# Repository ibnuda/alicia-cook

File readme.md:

# alicia cook

yet another uninspiring, boring, and beaten to death clone of alice "ergonomic"
keyboard. lol.

but, you should actually split it off and connect them using idc 2x5, tho.

## pics

## license
of course it's GPLv3.

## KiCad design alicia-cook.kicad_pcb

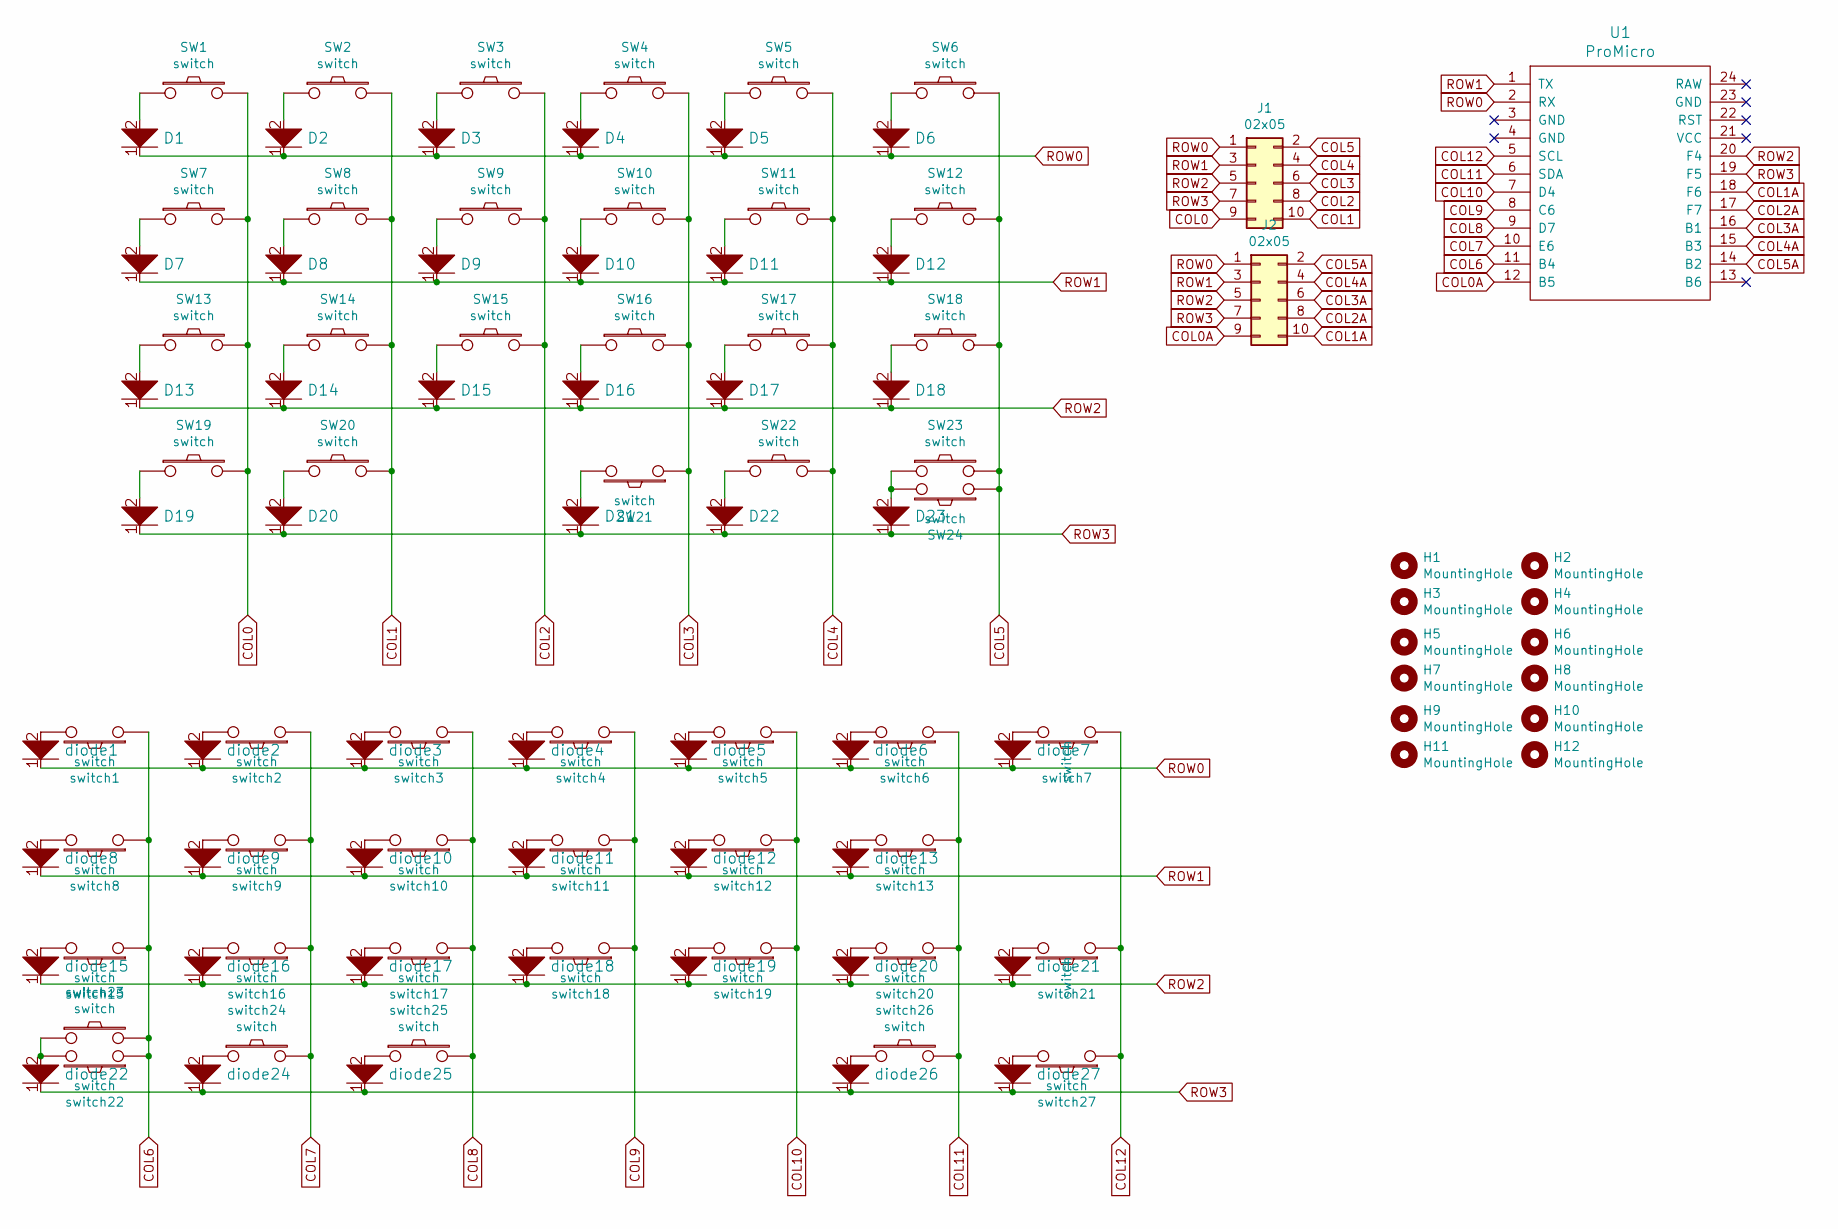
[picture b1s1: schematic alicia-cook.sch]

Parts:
D1, D2, D3, D4, D5, D6, D7, D8, D9, D10, D11, D12, D13, D14, D15, D16, D17, D18, D19, D20, D21, D22, D23: D; diode
H1, H3: MountingHole; hole-three-bigger
H2, H4, H5, H6, H7, H8, H9, H10, H11, H12: MountingHole; hole-three
J1, J2: 02x05; connector-shrouded
SW1, SW2, SW3, SW4, SW5, SW6, SW8, SW9, SW10, SW11, SW12, SW14, SW15, SW16, SW17, SW18, SW22, SW23: switch; 1u-minimal
SW7, SW19, SW20, SW21: switch; 125u-minimal
SW13: switch; 175u-minimal
SW24: switch; 2u-minimal
U1: ProMicro; promicro
diode1, diode2, diode3, diode4, diode5, diode6, diode7, diode8, diode9, diode10, diode11, diode12, diode13, diode15, diode16, diode17, diode18, diode19, diode20, diode21, diode22, diode24, diode25, diode26, diode27: diode
switch1, switch2, switch3, switch4, switch5, switch6, switch7, switch8, switch9, switch10, switch11, switch12, switch15, switch16, switch17, switch18, switch19, switch20, switch24, switch25: switch; 1u-minimal
switch13: switch; 175u-minimal
switch21, switch22, switch26, switch27: switch; 125u-minimal
switch23: switch; 225u-minimal

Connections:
COL0: J1.9, SW1.2, SW7.2, SW13.2, SW19.2
COL0A: J2.9, U1.12 (B5)
COL1: J1.10, SW2.2, SW8.2, SW14.2, SW20.2
COL1A: J2.10, U1.18 (F6)
COL2: J1.8, SW3.2, SW9.2, SW15.2
COL2A: J2.8, U1.17 (F7)
COL3: J1.6, SW4.2, SW10.2, SW16.2, SW21.1
COL3A: J2.6, U1.16 (B1)
COL4: J1.4, SW5.2, SW11.2, SW17.2, SW22.2
COL4A: J2.4, U1.15 (B3)
COL5: J1.2, SW6.2, SW12.2, SW18.2, SW23.2, SW24.1
COL5A: J2.2, U1.14 (B2)
COL6: U1.11 (B4), switch1.1, switch8.1, switch15.1, switch22.1, switch23.2
COL7: U1.10 (E6), switch2.1, switch9.1, switch16.1, switch24.2
COL8: U1.9 (D7), switch3.1, switch10.1, switch17.1, switch25.2
COL9: U1.8 (C6), switch4.1, switch11.1, switch18.1
COL10: U1.7 (D4), switch5.1, switch12.1, switch19.1
COL11: U1.6 (SDA), switch6.1, switch13.1, switch20.1, switch26.2
COL12: U1.5 (SCL), switch7.1, switch21.1, switch27.1
unnamed: D1.2, SW1.1
unnamed: D2.2, SW2.1
unnamed: D3.2, SW3.1
unnamed: D4.2, SW4.1
unnamed: D5.2, SW5.1
unnamed: D6.2, SW6.1
unnamed: D7.2, SW7.1
unnamed: D8.2, SW8.1
unnamed: D9.2, SW9.1
unnamed: D10.2, SW10.1
unnamed: D11.2, SW11.1
unnamed: D12.2, SW12.1
unnamed: D13.2, SW13.1
unnamed: D14.2, SW14.1
unnamed: D15.2, SW15.1
unnamed: D16.2, SW16.1
unnamed: D17.2, SW17.1
unnamed: D18.2, SW18.1
unnamed: D19.2, SW19.1
unnamed: D20.2, SW20.1
unnamed: D21.2, SW21.2
unnamed: D22.2, SW22.1
unnamed: D23.2, SW23.1, SW24.2
unnamed: diode1.2, switch1.2
unnamed: diode2.2, switch2.2
unnamed: diode3.2, switch3.2
unnamed: diode4.2, switch4.2
unnamed: diode5.2, switch5.2
unnamed: diode6.2, switch6.2
unnamed: diode7.2, switch7.2
unnamed: diode8.2, switch8.2
unnamed: diode9.2, switch9.2
unnamed: diode10.2, switch10.2
unnamed: diode11.2, switch11.2
unnamed: diode12.2, switch12.2
unnamed: diode13.2, switch13.2
unnamed: diode15.2, switch15.2
unnamed: diode16.2, switch16.2
unnamed: diode17.2, switch17.2
unnamed: diode18.2, switch18.2
unnamed: diode19.2, switch19.2
unnamed: diode20.2, switch20.2
unnamed: diode21.2, switch21.2
unnamed: diode22.2, switch22.2, switch23.1
unnamed: diode24.2, switch24.1
unnamed: diode25.2, switch25.1
unnamed: diode26.2, switch26.1
unnamed: diode27.2, switch27.2
ROW0: D1.1, D2.1, D3.1, D4.1, D5.1, D6.1, J1.1, J2.1, U1.2 (RX), diode1.1, diode2.1, diode3.1, diode4.1, diode5.1, diode6.1, diode7.1
ROW1: D7.1, D8.1, D9.1, D10.1, D11.1, D12.1, J1.3, J2.3, U1.1 (TX), diode8.1, diode9.1, diode10.1, diode11.1, diode12.1, diode13.1
ROW2: D13.1, D14.1, D15.1, D16.1, D17.1, D18.1, J1.5, J2.5, U1.20 (F4), diode15.1, diode16.1, diode17.1, diode18.1, diode19.1, diode20.1, diode21.1
ROW3: D19.1, D20.1, D21.1, D22.1, D23.1, J1.7, J2.7, U1.19 (F5), diode22.1, diode24.1, diode25.1, diode26.1, diode27.1

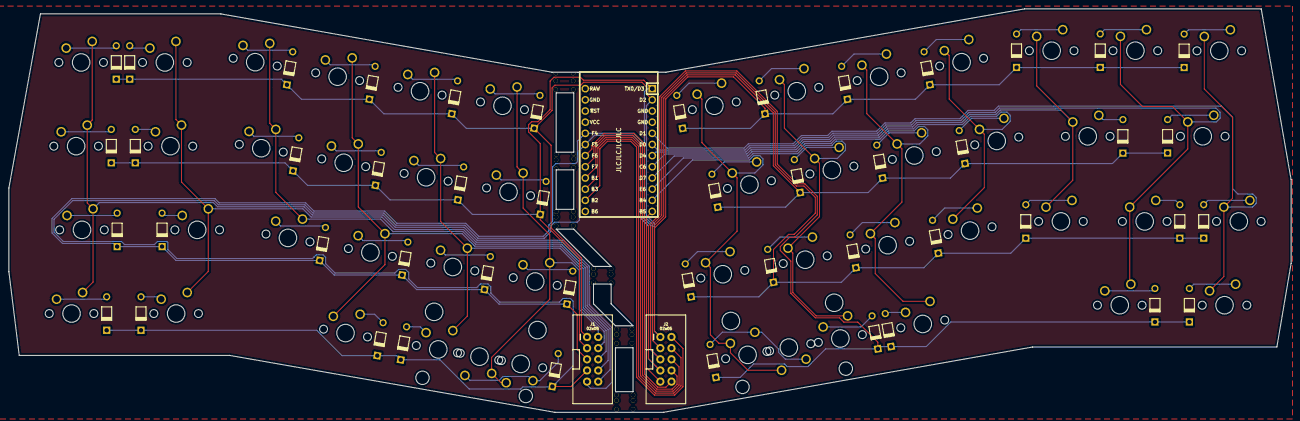
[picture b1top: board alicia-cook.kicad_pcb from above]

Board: 2 copper layers, 291.8 x 91.8 mm, 113 parts (1 on the bottom side), 71 nets.

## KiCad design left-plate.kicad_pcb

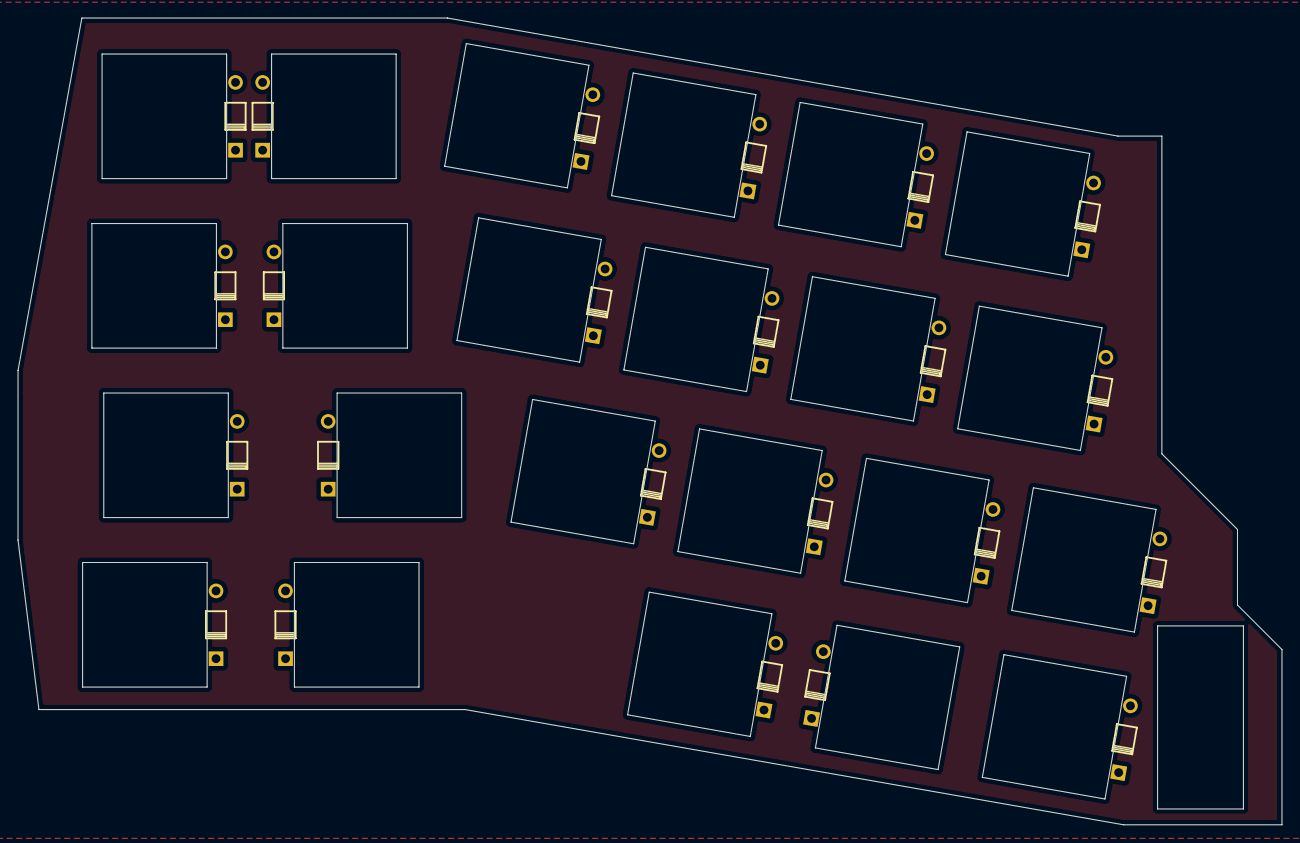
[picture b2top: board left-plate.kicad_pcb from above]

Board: 2 copper layers, 142.0 x 90.6 mm, 46 parts (0 on the bottom side), 4 nets, no tracks yet.

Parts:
D1, D2, D3, D4, D5, D6, D7, D8, D9, D10, D11, D12, D13, D14, D15, D16, D17, D18, D19, D20, D21, D22, D23: D; diode
SW1, SW2, SW3, SW4, SW5, SW6, SW7, SW8, SW9, SW10, SW11, SW12, SW13, SW14, SW15, SW16, SW17, SW18, SW19, SW20, SW21, SW22, SW23: switch; hole-switch

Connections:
ROW0: D1.1, D2.1, D3.1, D4.1, D5.1, D6.1
ROW1: D7.1, D8.1, D9.1, D10.1, D11.1, D12.1
ROW2: D13.1, D14.1, D15.1, D16.1, D17.1, D18.1
ROW3: D19.1, D20.1, D21.1, D22.1, D23.1

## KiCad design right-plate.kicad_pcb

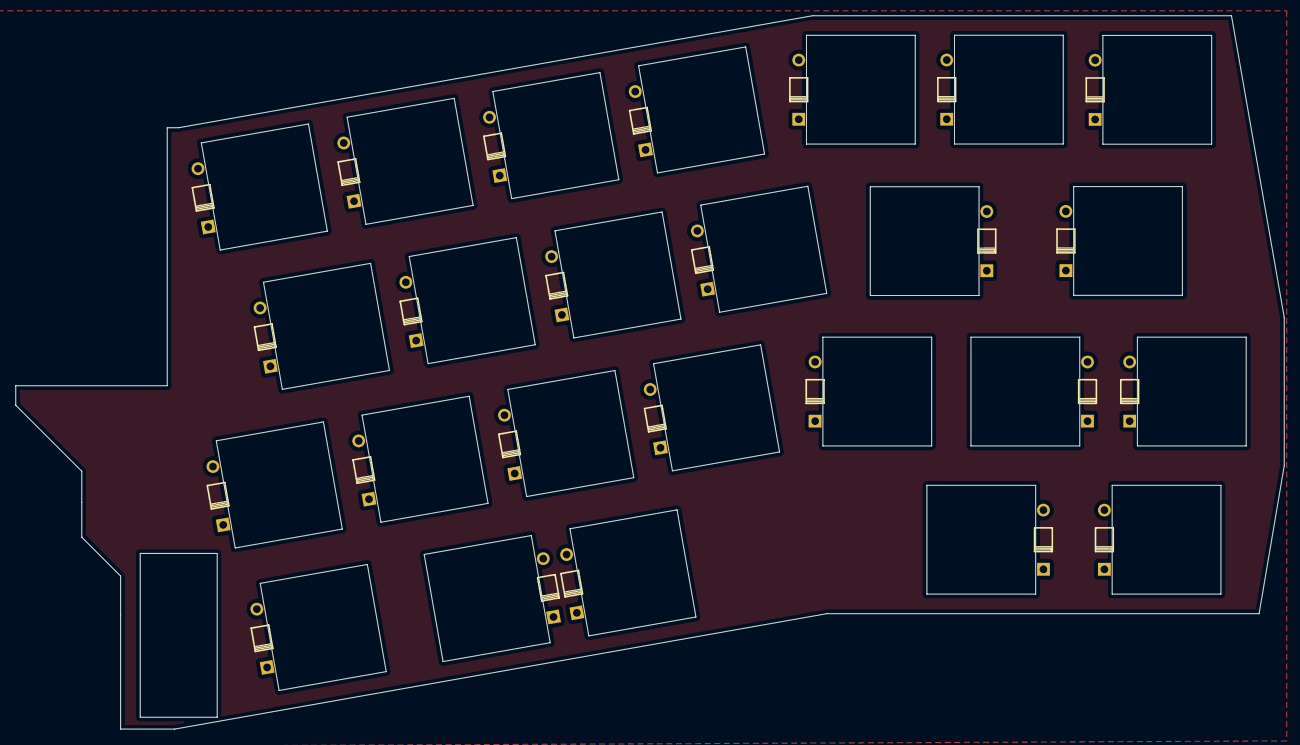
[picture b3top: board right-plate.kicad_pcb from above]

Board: 2 copper layers, 163.2 x 91.8 mm, 50 parts (0 on the bottom side), 4 nets, no tracks yet.

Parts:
diode1, diode2, diode3, diode4, diode5, diode6, diode7, diode8, diode9, diode10, diode11, diode12, diode13, diode15, diode16, diode17, diode18, diode19, diode20, diode21, diode22, diode24, diode25, diode26, diode27: diode
switch1, switch2, switch3, switch4, switch5, switch6, switch7, switch8, switch9, switch10, switch11, switch12, switch13, switch15, switch16, switch17, switch18, switch19, switch20, switch21, switch22, switch24, switch25, switch26, switch27: switch; hole-switch

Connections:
ROW0: diode1.1, diode2.1, diode3.1, diode4.1, diode5.1, diode6.1, diode7.1
ROW1: diode8.1, diode9.1, diode10.1, diode11.1, diode12.1, diode13.1
ROW2: diode15.1, diode16.1, diode17.1, diode18.1, diode19.1, diode20.1, diode21.1
ROW3: diode22.1, diode24.1, diode25.1, diode26.1, diode27.1

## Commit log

2021-01-19 init commit.
2021-01-19 something something.
2021-01-19 some wilding tracks smh my head.
2021-01-20 some route fixes.
2021-01-20 3d models.
2021-01-24 left and right switch plate.
2021-01-27 idk.
2021-01-29 good image.
2021-09-03 sandwich plates.
